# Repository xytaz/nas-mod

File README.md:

# NAS Mod

## Description

This project started with the objective to turn a USB RAID storage system into a NAS (Network-Attached Storage) unit. In reality, it was more of a (very much needed) exercise in embedded Linux.

The essence of the idea is to modify a [GR3680-SB3](https://www.raidsonic.de/products/external_cases/soho_raid/index_en.php?we_objectID=2984) by replacing the proprietary board with a Raspberry Pi or an ODROID-XU4. This involves:

  - Connecting the LCD, control buttons, and LED's to the new board(s) properly.
  - Interfacing Linux with this extra hardware.
  - Writing a piece of code to make use of it.

Given how surprisingly scarce, scattered, cryptic, or incomplete Linux resources on this subject can be (at least for an advanced beginner), this repo serves not only as a reference for this particular implementation but also as a tutorial for interacting with basic hardware in Linux. The emphasis is not on NAS software itself.

## Quick guide

There is a number of Makefile's to automate the setup. Keep in mind that several parameters are hard-coded and things may easily break. See the detailed documentation when that happens.

Assuming you have [Linux set up](docs/02-linux-setup.md) properly, clone this repo and run `make` in each of the following directories and then reboot at the end:

- Pi
    ```
    /code/02-device-tree/pi
    /code/03-python
    /code/04-systemd-service # (manually change path in Makefile)
    ```
- XU4
    ```
    /code/01-modules
        # make NAME=charlcd
        # make NAME=charlcd
        # echo 'charlcd' | sudo tee -a /etc/modules
        # echo 'hd44780' | sudo tee -a /etc/modules
        # sudo depmod

    /code/02-device-tree/xu4
    /code/03-python
    /code/04-systemd-service # (manually change path in Makefile)
    ```

## Detailed documentation

_aka: The Missing Tutorial on How to Use Basic Hardware in Linux_

- [Hardware](docs/01-hardware.md)
- [Linux setup](docs/02-linux-setup.md)
- [How to interact with GPIO's](docs/03-gpios.md)
- [Drivers and modules](docs/04-drivers-modules.md)
- [Device tree](docs/05-device-tree.md)
- [Testing](docs/06-testing.md)
- [Python](docs/07-python.md)
- [Auto-start script](docs/08-autostart.md)

## Known issues

- Jittery backlight on startup, power off, and more.
- LCD animation better when looking at some angles (but not straight on).
- Scrolling with values that change frequently (multiple values in a line or temperature).
- Clock skipping a second occasionally.
- Last message remains after power off then on
- Not sure where these default messages come from:
    - Kernel version on startup.
    - "Power off" on shutdown.
    - "LCD driver unloaded" when `hd44780` module is removed, e.g. with `rmmod`.
    - "Reloading System ..." on reboot.

## Gallery

_                   |_
--------------------|--------------------
 |  
 |  
 |

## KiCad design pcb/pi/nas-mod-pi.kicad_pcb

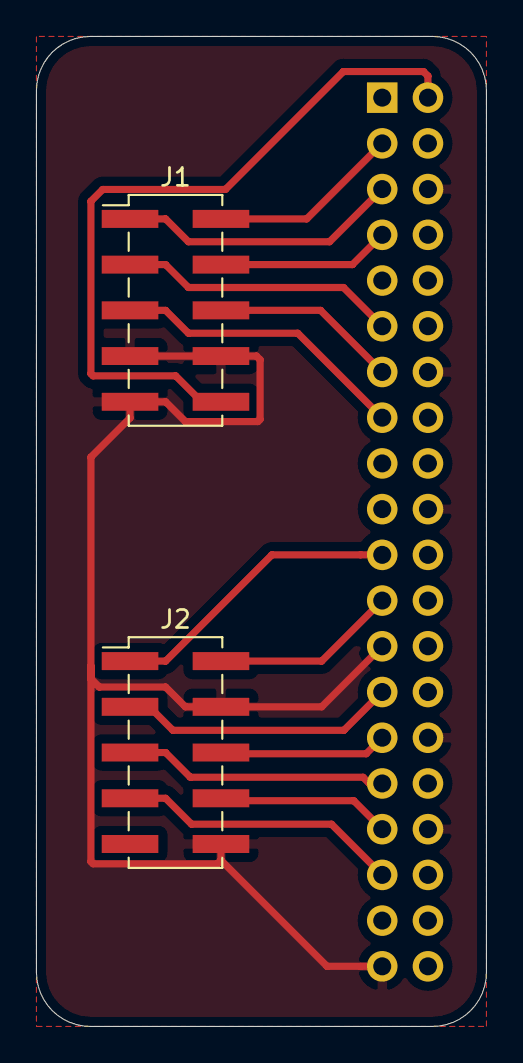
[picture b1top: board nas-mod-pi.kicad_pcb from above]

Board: 2 copper layers, 25.0 x 55.0 mm, 3 parts (1 on the bottom side), 16 nets.

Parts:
J1, J2: Conn_02x05_Odd_Even; PinHeader_2x05_P2.54mm_Vertical_SMD
J3: Conn_02x20_Odd_Even; PinSocket_2x20_P2.54mm_Vertical

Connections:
/3V3: J3.1, J3.17
/5V: J1.10, J3.2, J3.4
/D0: J1.3, J3.11
/D1: J1.4, J3.7
/D2: J1.1, J3.5
/D3: J1.2, J3.3
/EN: J1.6, J3.13
/GND: J1.7, J1.8, J1.9, J2.4, J2.10, J3.6, J3.9, J3.14, J3.20, J3.25, J3.30, J3.34, J3.39
/LED1: J2.6, J3.29
/LED2: J2.8, J3.33
/RST: J1.5, J3.15
/SW1a: J2.2, J3.23
/SW2: J2.7, J3.35
/SW3: J2.5, J3.31
/SW4: J2.1, J3.21
/SW5: J2.3, J3.27

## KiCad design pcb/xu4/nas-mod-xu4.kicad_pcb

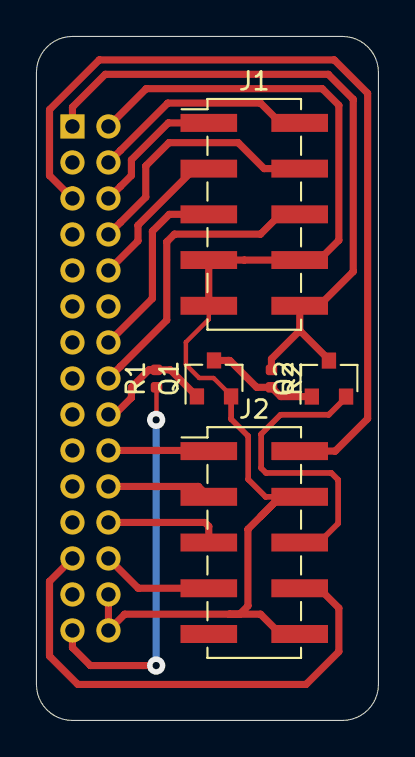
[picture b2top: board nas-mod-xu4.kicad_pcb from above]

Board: 2 copper layers, 19.0 x 38.0 mm, 7 parts (1 on the bottom side), 18 nets.

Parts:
J1, J2: Conn_02x05_Odd_Even; PinHeader_2x05_P2.54mm_Vertical_SMD
J3: Conn_02x15_Odd_Even; PinSocket_2x15_P2.00mm_Vertical
Q1, Q2: BSS138; SOT-23
R1, R2: 10K; R_0402_1005Metric

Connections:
/1V8: J3.29, R1.1
/5V: J1.10, J3.1, Q2.3, R2.1
/D4: J1.3, J3.10
/D5: J1.4, J3.8
/D6: J1.1, J3.6
/D7: J1.2, J3.4
/EN: J1.6, J3.16
/GND: J1.7, J1.8, J1.9, J2.4, J2.10, J3.2, J3.28, J3.30, Q1.2
/LED1: J2.6, Q2.2
/LED1-SGNL: J3.18, Q1.1, R1.2
/LED2: J2.8, J3.25
/RST: J1.5, J3.14
/SW1a: J2.2, J3.5
/SW2: J2.7, J3.26
/SW3: J2.5, J3.24
/SW4: J2.1, J3.20
/SW5: J2.3, J3.22
unnamed: Q1.3, Q2.1, R2.2

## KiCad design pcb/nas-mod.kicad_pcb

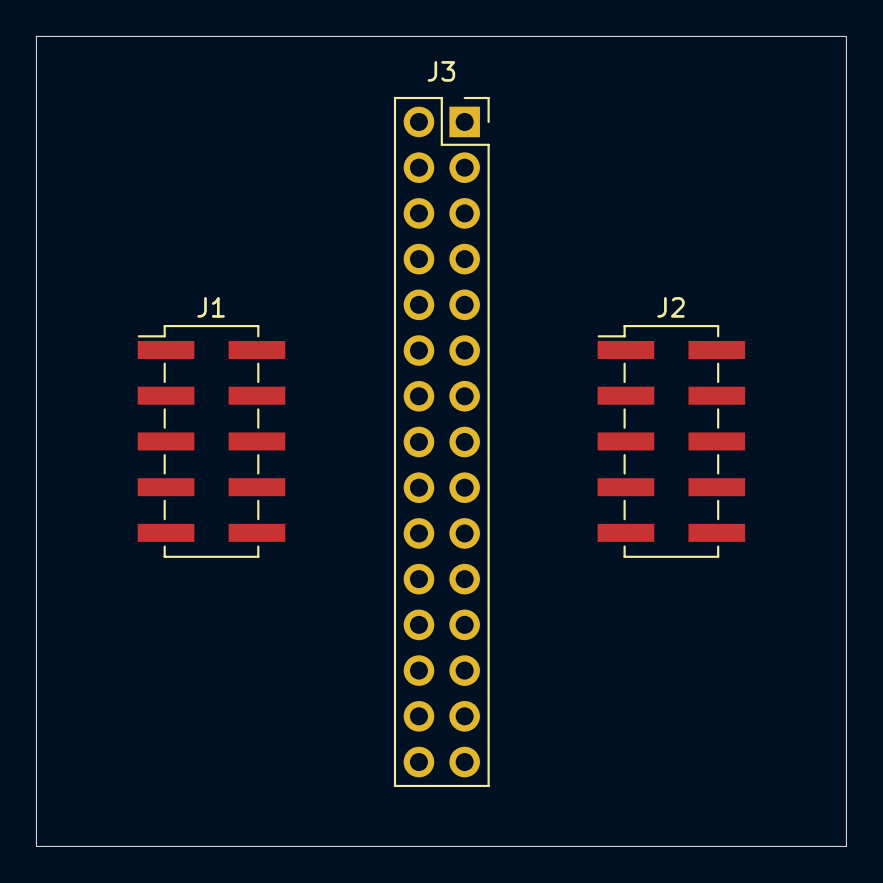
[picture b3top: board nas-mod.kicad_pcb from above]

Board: 2 copper layers, 45.0 x 45.0 mm, 3 parts (0 on the bottom side), 16 nets, no tracks yet.

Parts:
J1, J2: Conn_02x05_Odd_Even; PinHeader_2x05_P2.54mm_Vertical_SMD
J3: Conn_02x15_Odd_Even; PinSocket_2x15_P2.54mm_Vertical

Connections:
/5V: J1.10, J3.1
/D0: J1.3, J3.11
/D1: J1.4, J3.13
/D2: J1.1, J3.15
/D3: J1.2, J3.17
/EN: J1.5, J3.27
/GND: J1.7, J1.8, J2.10, J3.2, J3.28, J3.30
/LED1: J2.6, J3.4
/LED2: J2.8, J3.6
/RST: J1.6, J3.25
/SW1a: J2.2, J3.8
/SW1b: J2.4, J3.10
/SW2: J2.7, J3.20
/SW3: J2.5, J3.22
/SW4: J2.1, J3.24
/SW5: J2.3, J3.26

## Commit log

2019-12-21 Formatting changes to README
2020-01-22 Massive commit
